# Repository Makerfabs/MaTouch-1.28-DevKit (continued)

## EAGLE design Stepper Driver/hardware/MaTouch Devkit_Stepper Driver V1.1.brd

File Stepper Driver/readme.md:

# MaTouch1.28" Devkit Stepper Driver

```c++
/*
Library version:
Arduino IDE 2.3.4
esp32 V3.1.1
GFX Library for Arduino v1.5.4
lvgl v8.3.11
RTClib v2.1.4
Adafruit BusIO v1.16.2
ESP32Time v2.0.6

Tools:
USB CDC On Boot: Enabled
Flash size: 16MB(128Mb)
Partition Schrme: 16M Flash(3MB APP/9.9MB FATFS)
PSRAM: OPI PSRAM
*/
```
## Introduce

1.[How to use?](https://wiki.makerfabs.com/Matouch%201.28%20DevKit.html#25-step-motor-driver)

2.[How to upload code?](https://wiki.makerfabs.com/Matouch%201.28%20DevKit.html#35-step-motor-driver)

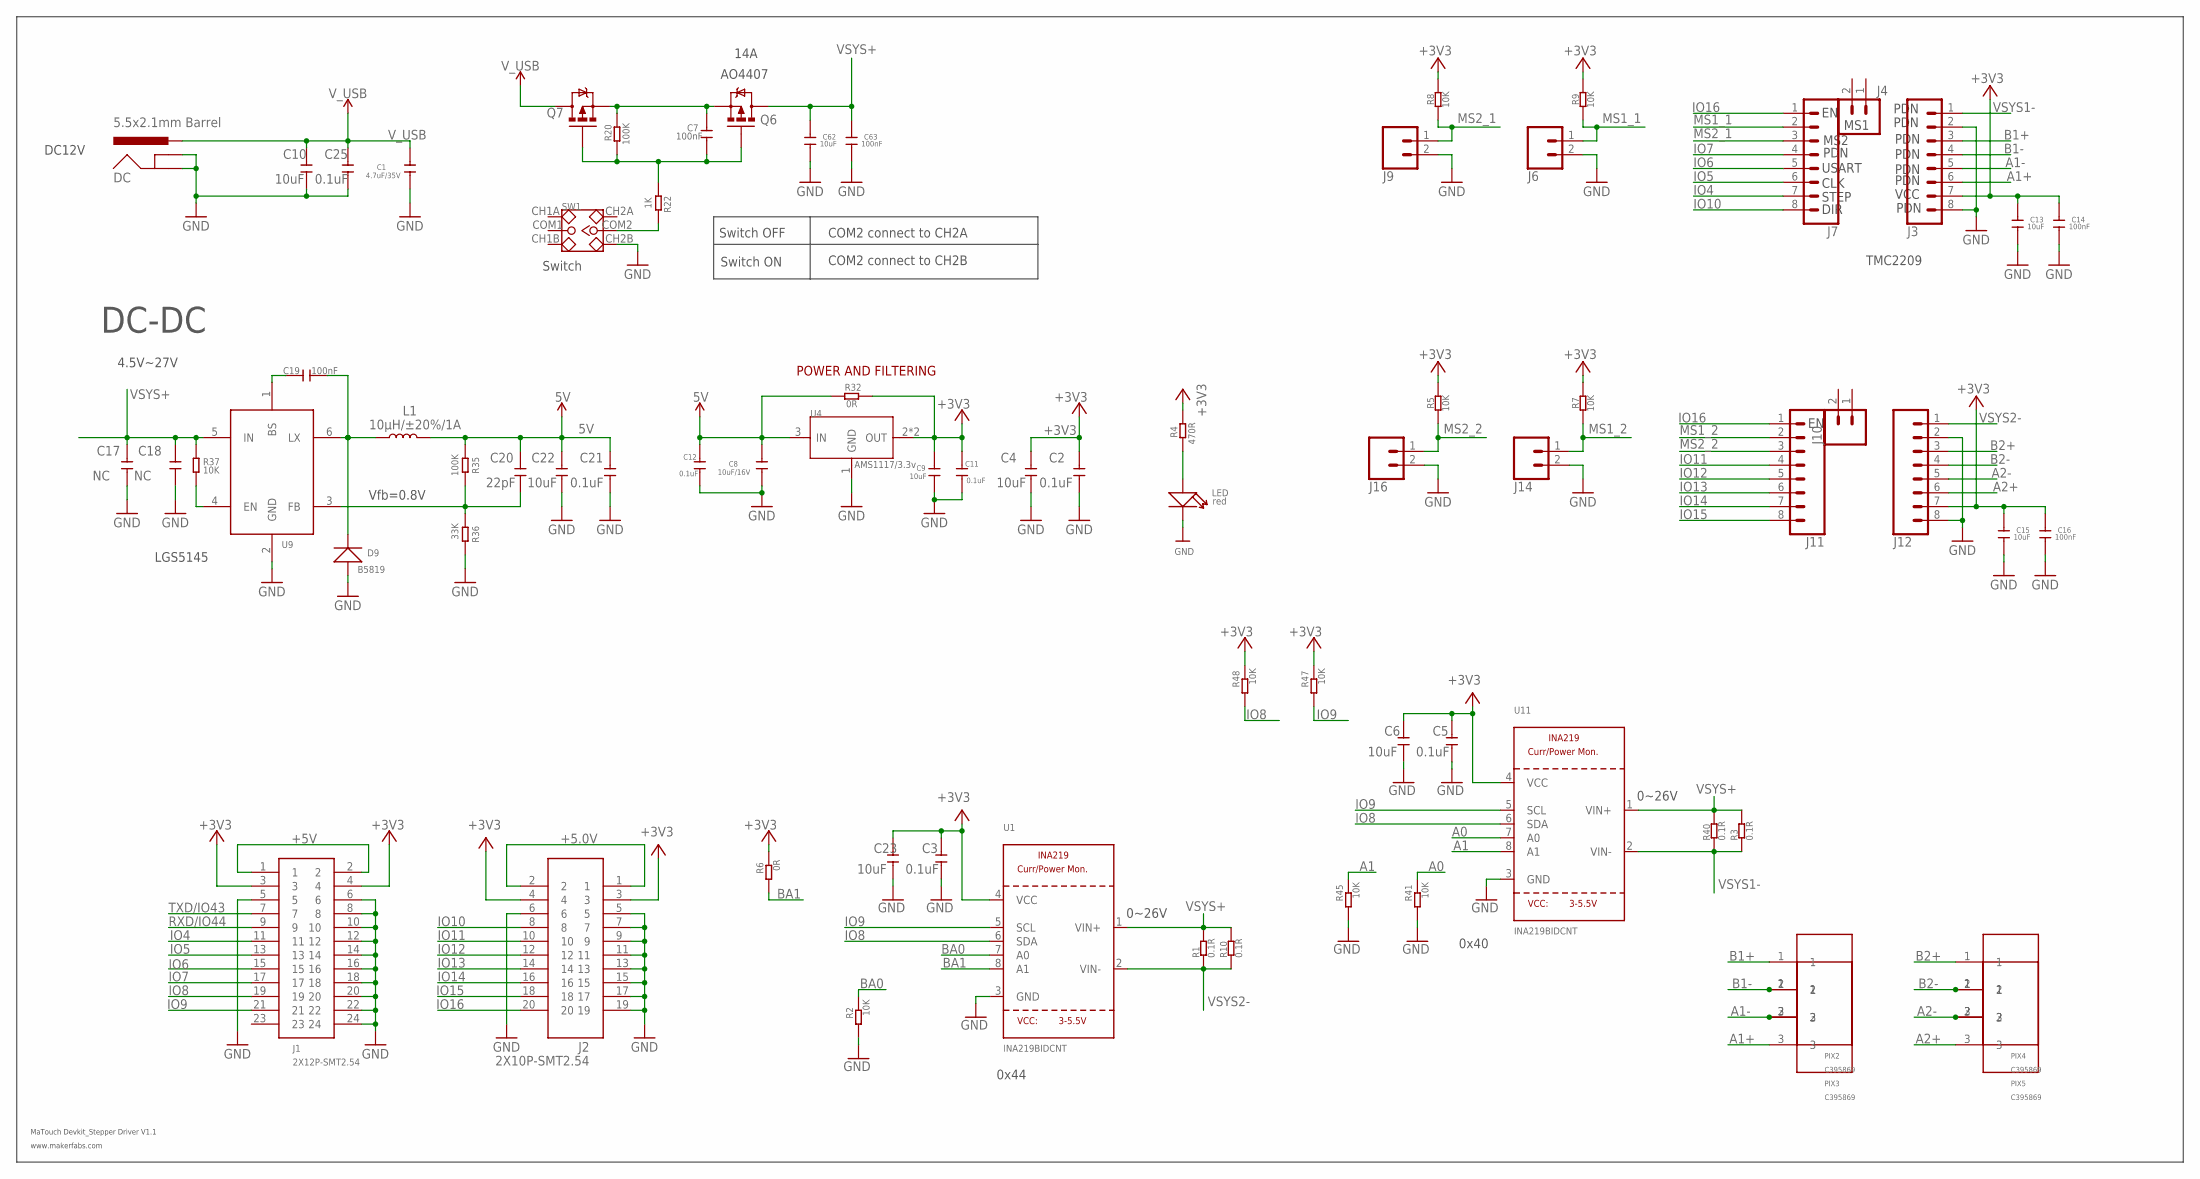
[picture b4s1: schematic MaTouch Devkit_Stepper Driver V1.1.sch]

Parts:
C1: 4.7uF/35V; 0603
C2, C3, C5, C11, C12, C21, C25: 0.1uF; 0603
C4, C6, C9, C10, C13, C15, C22, C23, C62: 10uF; 0603
C7, C14, C16, C19, C63: 100nF; 0603
C8: 10uF/16V; 0603
C17, C18: NC; 0603
C20: 22pF; 0603
D9: B5819; SOD123
DC: 5.5x2.1mm Barrel; POWER_JACK_SMD
J1: 2X12P-SMT2.54
J2: 2X10P-SMT2.54
J3, J7, J11, J12: CONN_08"; 1X08
J4, J6, J9, J10, J14, J16: CONN_02LOCK; 1X02_LOCK
L1: 10µH/±20%/1A; SRN6045
LED: red; DISCRETE_LED-0603
PIX2, PIX3, PIX4, PIX5: C395869; PIN_3P
Q6, Q7: MOSFET-PCHANNELFDS6675; SO08
R1, R3, R10, R40: 0.1R; DISCRETE_R2512
R2, R5, R7, R8, R9, R37, R41, R45, R47, R48: 10K; R0603
R4: 470R; R0603
R6, R32: 0R; R0603
R20, R35: 100K; R0603
R22: 1K; R0603
R36: 33K; R0603
SW1: SWITCH-2CH-6P'90D'; 6P-2CH-2.54-9.0X3.6-90D
U1, U11: INA219BIDCNT; SOT23-8
U4: AMS1117/3.3v; SOT89
U9: SY8201ABC; SOT-23-6

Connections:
5V: C8.1, C12.2, C20.2, C21.2, C22.2, L1.2, R32.1, R35.1, U4.3 (IN)
+3V3: C2.2, C3.2, C4.2, C5.2, C6.2, C9.1, C11.2, C13.2, C14.2, C15.2, C16.2, C23.2, J1.3, J1.4, J2.3, J2.4, J3.7, J12.7, R4.2, R5.2, R6.2, R7.2, R8.2, R9.2, R32.2, R47.2, R48.2, U1.4 (VCC), U4.2 (OUT), U4.4 (OUT), U11.4 (VCC)
+5.0V: J2.1, J2.2
+5V: J1.1, J1.2
A0: R41.2, U11.7 (A0)
A1: R45.2, U11.8 (A1)
A1+: J3.6, PIX3.3
A1-: J3.5, PIX2.3, PIX3.2
A2+: J12.6, PIX5.3
A2-: J12.5, PIX4.3, PIX5.2
B1+: J3.3, PIX2.1
B1-: J3.4, PIX2.2, PIX3.1
B2+: J12.3, PIX4.1
B2-: J12.4, PIX4.2, PIX5.1
BA0: R2.2, U1.7 (A0)
BA1: R6.1, U1.8 (A1)
GND: C1.2, C2.1, C3.1, C4.1, C5.1, C6.1, C8.2, C9.2, C10.1, C11.1, C12.1, C13.1, C14.1, C15.1, C16.1, C17.1, C18.1, C21.1, C22.1, C23.1, C25.1, C62.1, C63.1, D9.+, DC.GND (GNDBREAK), DC.P$4 (GND), J1.5, J1.6, J1.8, J1.10, J1.12, J1.14, J1.16, J1.18, J1.20, J1.22, J1.24, J2.5, J2.6, J2.7, J2.9, J2.11, J2.13, J2.15, J2.17, J2.19, J3.2, J3.8, J6.2, J9.2, J12.2, J12.8, J14.2, J16.2, LED.-, R2.1, R36.2, R41.1, R45.1, SW1.CH2B, U1.3 (GND), U4.1 (GND), U9.2 (GND), U11.3 (GND)
IO4: J1.11, J7.7
IO5: J1.13, J7.6
IO6: J1.15, J7.5
IO7: J1.17, J7.4
IO8: J1.19, R48.1, U1.6 (SDA), U11.6 (SDA)
IO9: J1.21, R47.1, U1.5 (SCL), U11.5 (SCL)
IO10: J2.8, J7.8
IO11: J2.10, J11.4
IO12: J2.12, J11.5
IO13: J2.14, J11.6
IO14: J2.16, J11.7
IO15: J2.18, J11.8
IO16: J2.20, J7.1, J11.1
MS1_1: J6.1, J7.2, R9.1
MS1_2: J11.2, J14.1, R7.1
MS2_1: J7.3, J9.1, R8.1
MS2_2: J11.3, J16.1, R5.1
unnamed: LED.+, R4.1
unnamed: C7.1, Q6.4 (G), Q7.4 (G), R20.2, R22.2
unnamed: R22.1, SW1.COM2
unnamed: C19.2, D9.-, L1.1, U9.6 (LX)
unnamed: C19.1, U9.1 (BS)
unnamed: C20.1, R35.2, R36.1, U9.3 (FB)
unnamed: R37.2, U9.4 (EN)
unnamed: C7.2, Q6.1 (S), Q6.2 (S), Q6.3 (S), Q7.1 (S), Q7.2 (S), Q7.3 (S), R20.1
RXD/IO44: J1.9
TXD/IO43: J1.7
VSYS1-: J3.1, R3.1, R40.1, U11.2 (VIN-)
VSYS2-: J12.1, R1.1, R10.1, U1.2 (VIN-)
VSYS+: C17.2, C18.2, C62.2, C63.2, Q6.5 (D), Q6.6 (D), Q6.7 (D), Q6.8 (D), R1.2, R3.2, R10.2, R37.1, R40.2, U1.1 (VIN+), U9.5 (IN), U11.1 (VIN+)
V_USB: C1.1, C10.2, C25.2, DC.VIN0 (PWR), Q7.5 (D), Q7.6 (D), Q7.7 (D), Q7.8 (D)

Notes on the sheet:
MaTouch Devkit_Stepper Driver V1.1
www.makerfabs.com
DC-DC
Switch OFF
Switch ON
COM2 connect to CH2A
COM2 connect to CH2B
Vfb=0.8V
4.5V~27V
0~26V
DC12V
AO4407
14A
Switch
POWER AND FILTERING
PDN
USART
CLK
STEP
DIR
VCC
MS1
MS2
LGS5145
TMC2209
0x40
0x44

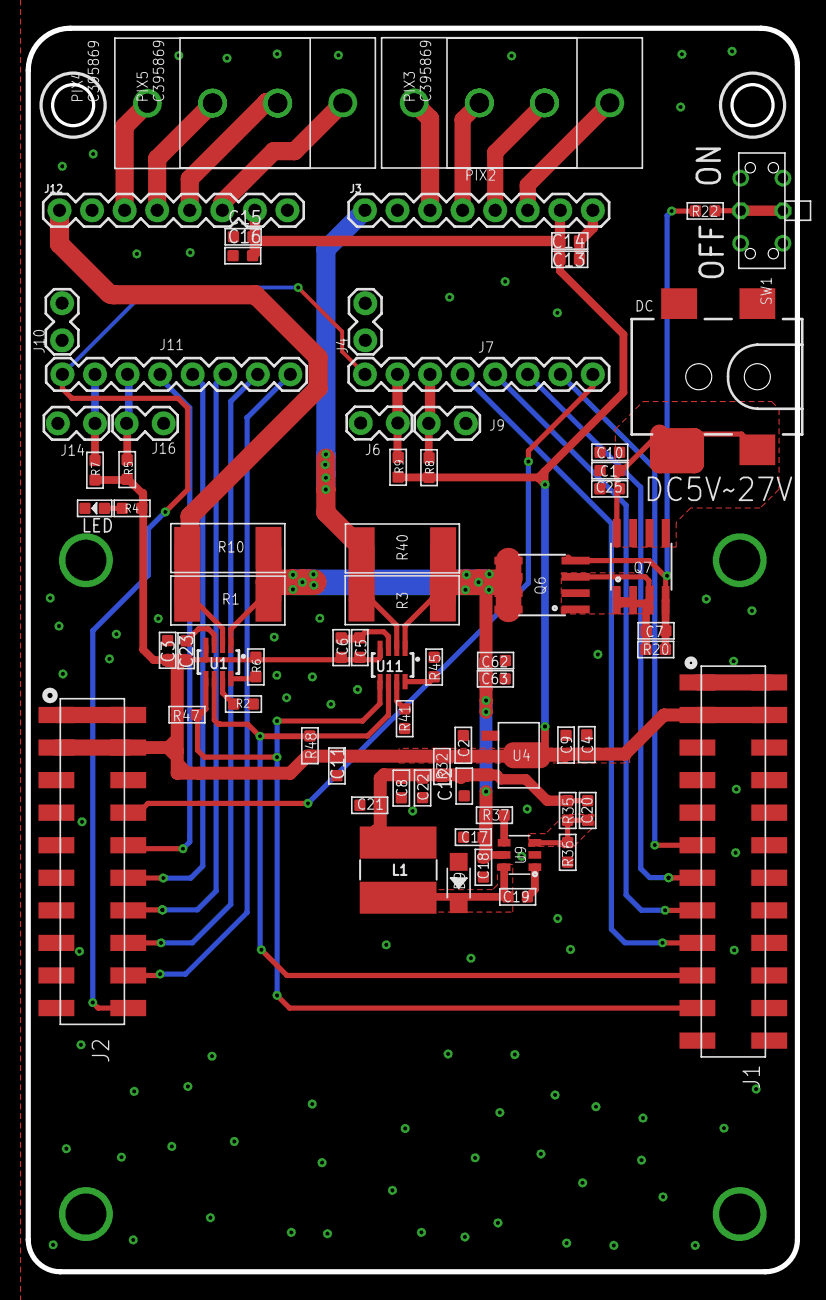
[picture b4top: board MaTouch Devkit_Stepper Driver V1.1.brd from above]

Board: 2 copper layers, 60.0 x 97.0 mm, 75 parts (1 on the bottom side), 46 nets.

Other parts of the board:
U$2: MAKERFABS_0.3

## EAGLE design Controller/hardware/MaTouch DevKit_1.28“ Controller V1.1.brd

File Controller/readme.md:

# MaTouch1.28" DevKit Controller

## Intruduce

The MaTouch 1.28" ToolSet_Controller is an ESP32-S3-based round touch controller, with haptic feedback, RTC, and more expansion interfaces for a smarter and richer interactive experience.

[YouTube Video](https://youtu.be/dvfv04e7QA0)

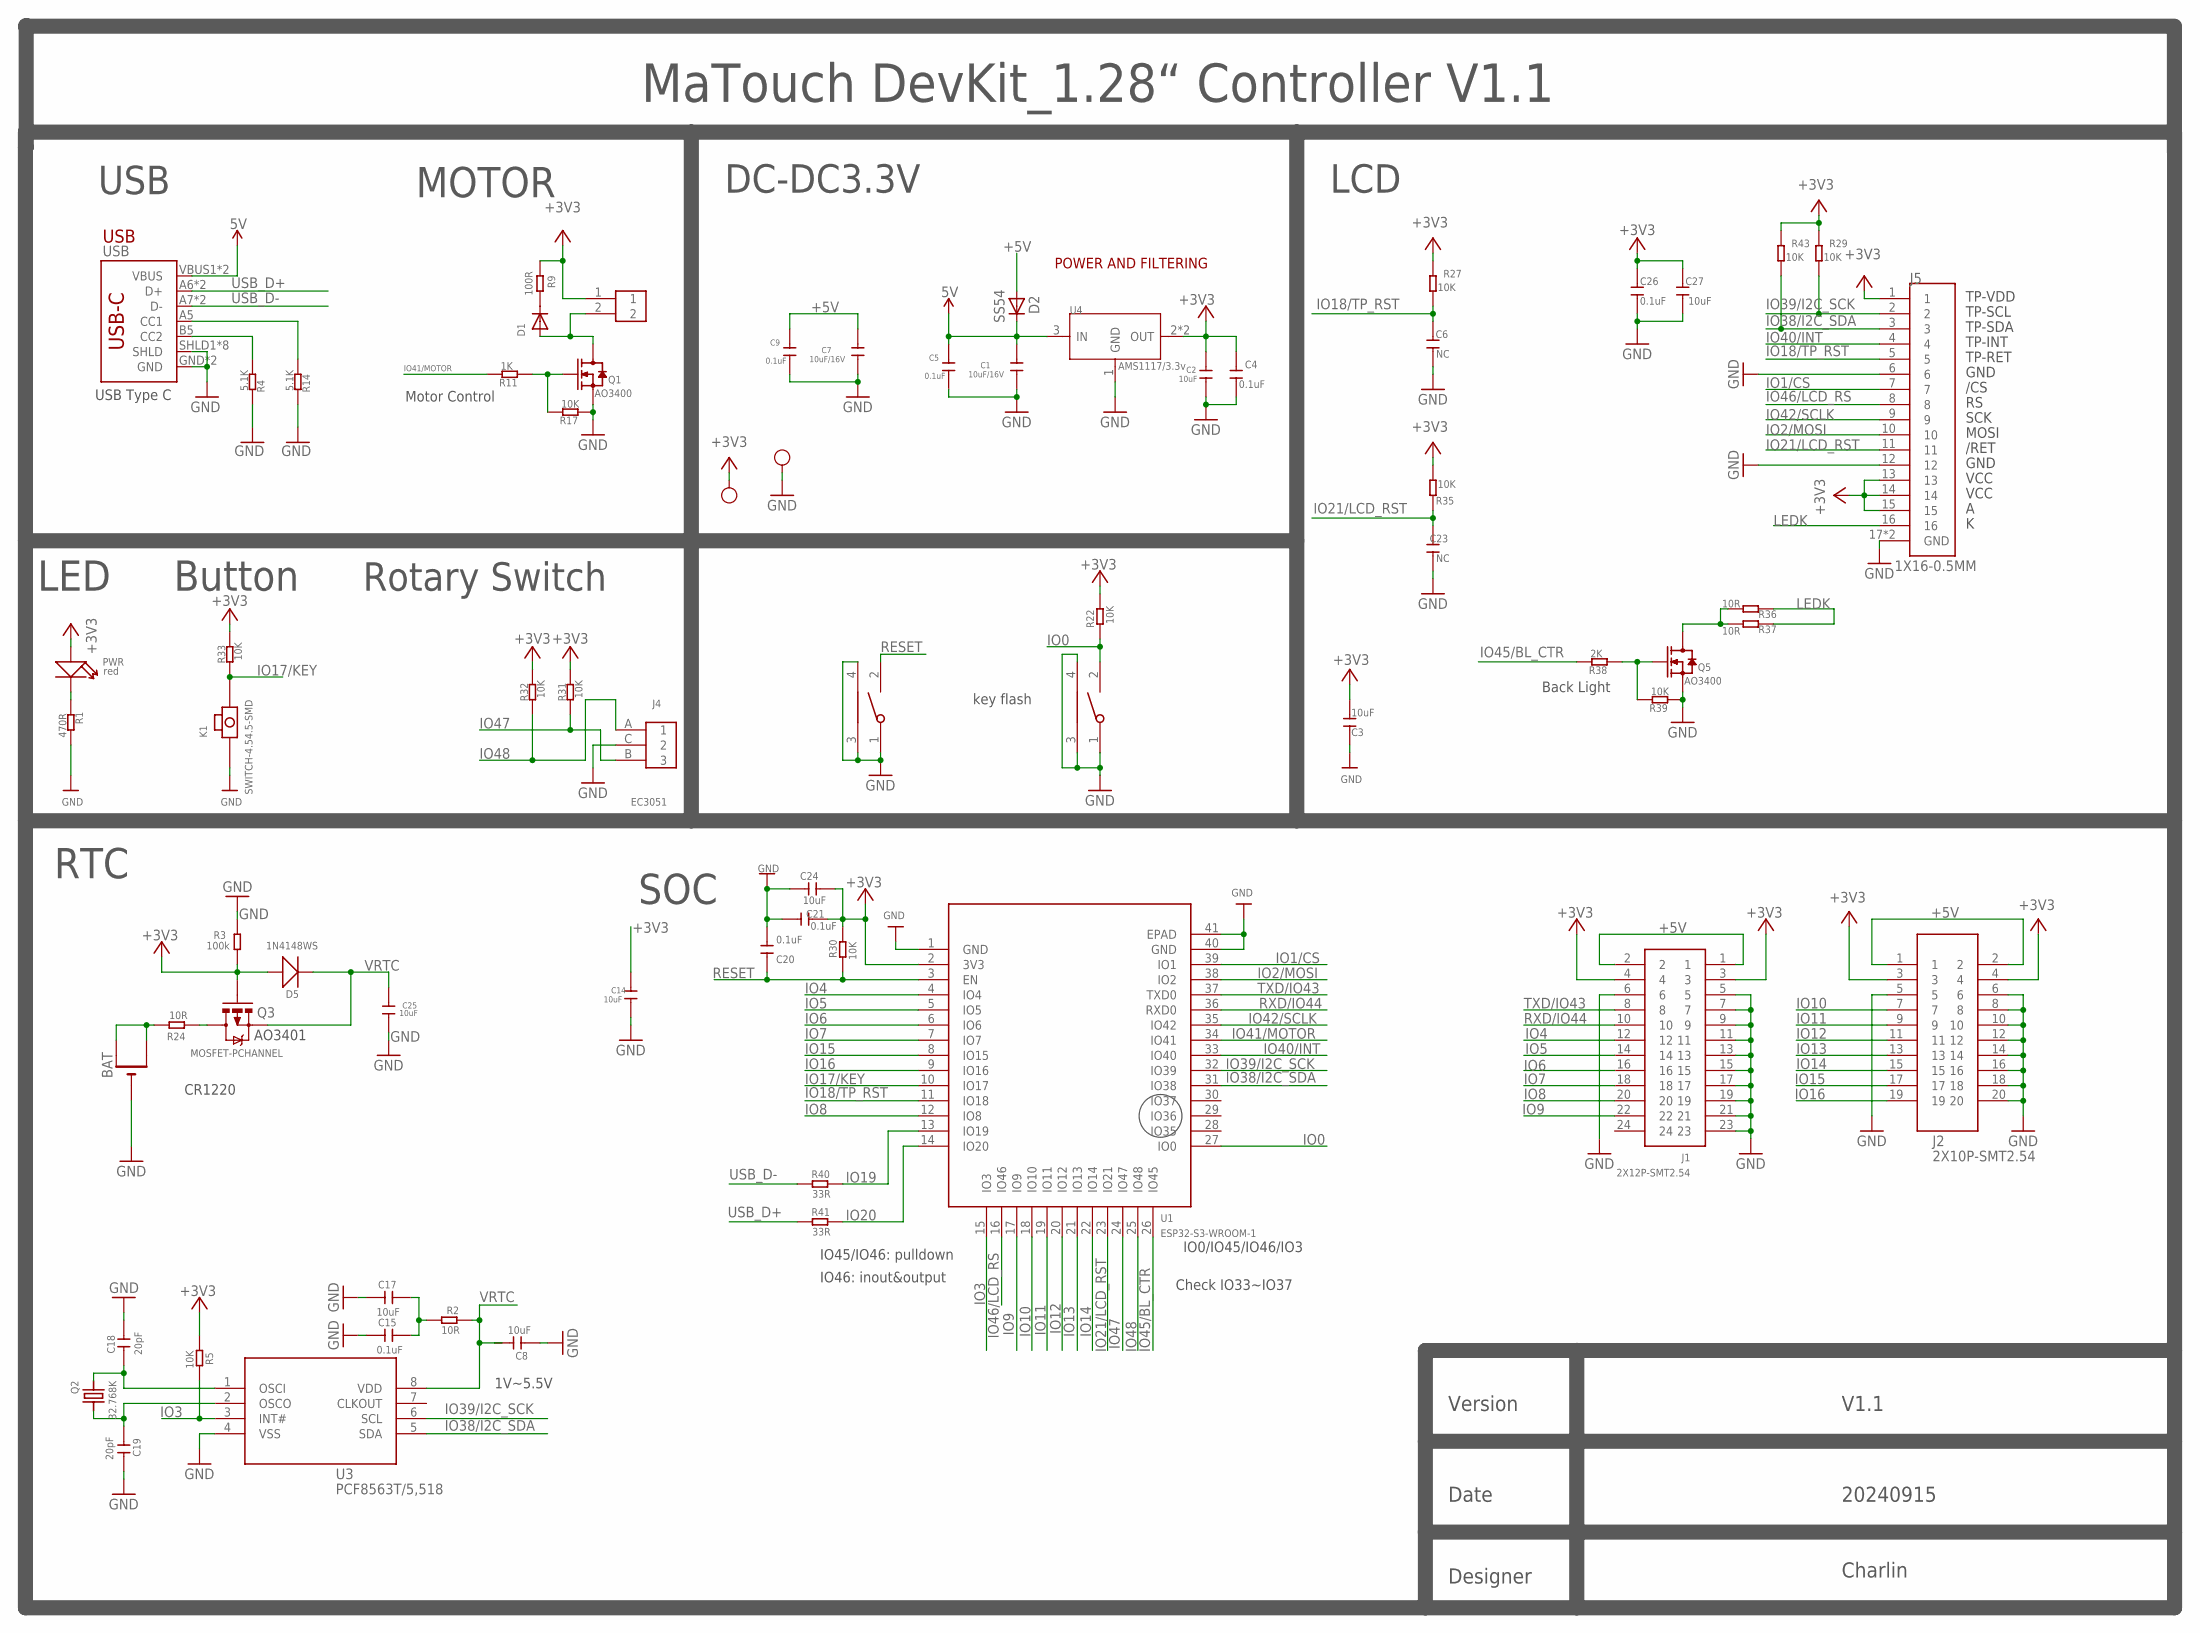
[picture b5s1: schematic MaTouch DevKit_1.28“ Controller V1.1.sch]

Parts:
3V3: TEST-POINT'4545'; TP-D45MIL; PARTNO DNP
BAT: CR1220SMT; CR1220-SMD
BOOT: TS24CA; 2*4*3.5MM
C1, C7: 10uF/16V; 0603
C2, C14, C25: 10uF; 0603
C3, C8, C17, C24: 10uF; DISCRETE_C0603
C4, C26: 0.1uF; DISCRETE_C0402
C5, C9: 0.1uF; 0603
C6, C23: NC; DISCRETE_C0402
C15, C20, C21: 0.1uF; DISCRETE_C0603
C18, C19: 20pF; DISCRETE_C0603
C27: 10uF; DISCRETE_C0402
D1: DIODESOD-323F; SOD-323F
D2: SS54; DO-214AC
D5: 1N4148WS; SOD323
GND: TEST-POINT'4545'; TP-D45MIL; PARTNO DNP
J1: 2X12P-SMT2.54
J2: 2X10P-SMT2.54
J4: EC3051; MAKERFABS_EC3051
J5: 1X16-0.5MM
K1: SWITCH-4.54.5-SMD; SWITCH-4.5*4.5-SMD
MOTOR: CN-1.02P; SH1.0-2P-SMD
PWR: red; DISCRETE_LED-0603
Q1, Q5: AO3400; SOT23@1
Q2: 32.768K; XTAL3215
Q3: MOSFET-PCHANNEL; SOT23-3
R1: 470R; DISCRETE_R0402
R2, R24: 10R; R0603
R3: 100k; R0603
R4, R14: 5.1K; DISCRETE_R0402
R5, R22, R30: 10K; R0603
R9: 100R; DISCRETE_R0402
R11: 1K; DISCRETE_R0402
R17, R27, R29, R31, R32, R33, R35, R39, R43: 10K; DISCRETE_R0402
R36, R37: 10R; DISCRETE_R0402
R38: 2K; DISCRETE_R0402
R40, R41: 33R; R0603
RST: TS24CA; 2*4*3.5MM
U1: ESP32-S3-WROOM-1
U3: PCF8563T/5,518; SOP8
U4: AMS1117/3.3v; SOT89
USB: USB_C5; USB-C-16P-5

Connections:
5V: C1.1, C5.1, D2.C, U4.3 (IN), USB.VBUS1 (VBUS), USB.VBUS2 (VBUS)
+3V3: 3V3.T, C2.1, C3.2, C4.2, C14.1, C21.1, C24.1, C26.2, C27.2, D5.+, J1.3, J1.4, J2.3, J2.4, J5.1, J5.13, J5.14, J5.15, MOTOR.1, PWR.+, Q3.1 (G), R3.1, R5.1, R9.1, R22.2, R27.2, R29.2, R30.2, R31.1, R32.1, R33.1, R35.2, R43.2, U1.2 (3V3), U4.2 (OUT), U4.4 (OUT)
+5V: C7.1, C9.1, D2.A, J1.1, J1.2, J2.1, J2.2
GND: BAT.-, BOOT.1, BOOT.3, BOOT.4, C1.2, C2.2, C3.1, C4.1, C5.2, C6.1, C7.2, C8.1, C9.2, C14.2, C15.1, C17.1, C18.2, C19.2, C20.2, C21.2, C23.1, C24.2, C25.1, C26.1, C27.1, GND.T, J1.5, J1.6, J1.7, J1.9, J1.11, J1.13, J1.15, J1.17, J1.19, J1.21, J1.23, J2.5, J2.6, J2.8, J2.10, J2.12, J2.14, J2.16, J2.18, J2.20, J4.C (2), J5.6, J5.12, J5.17 (GND), J5.18 (GND), K1.1, K1.4 (1), Q1.2 (S), Q5.2 (S), R1.1, R3.2, R4.2, R14.2, R17.1, R39.1, RST.1, RST.3, RST.4, U1.1 (GND), U1.40 (GND), U1.41 (EPAD), U3.4 (VSS), U4.1 (GND), USB.GND, USB.GND2 (GND), USB.SHLD1 (SHLD), USB.SHLD2 (SHLD), USB.SHLD3 (SHLD), USB.SHLD4 (SHLD), USB.SHLD5 (SHLD), USB.SHLD6 (SHLD), USB.SHLD7 (SHLD), USB.SHLD8 (SHLD)
IO0: BOOT.2, R22.1, U1.27 (IO0)
IO1/CS: J5.7, U1.39 (IO1)
IO2/MOSI: J5.10, U1.38 (IO2)
IO3: R5.2, U1.15 (IO3), U3.3 (INT#)
IO4: J1.12, U1.4 (IO4)
IO5: J1.14, U1.5 (IO5)
IO6: J1.16, U1.6 (IO6)
IO7: J1.18, U1.7 (IO7)
IO8: J1.20, U1.12 (IO8)
IO9: J1.22, U1.17 (IO9)
IO10: J2.7, U1.18 (IO10)
IO11: J2.9, U1.19 (IO11)
IO12: J2.11, U1.20 (IO12)
IO13: J2.13, U1.21 (IO13)
IO14: J2.15, U1.22 (IO14)
IO15: J2.17, U1.8 (IO15)
IO16: J2.19, U1.9 (IO16)
IO17/KEY: K1.2, K1.3 (2), R33.2, U1.10 (IO17)
IO18/TP_RST: C6.2, J5.5, R27.1, U1.11 (IO18)
IO19: R40.2, U1.13 (IO19)
IO20: R41.2, U1.14 (IO20)
IO21/LCD_RST: C23.2, J5.11, R35.1, U1.23 (IO21)
IO38/I2C_SDA: J5.3, R43.1, U1.31 (IO38), U3.5 (SDA)
IO39/I2C_SCK: J5.2, R29.1, U1.32 (IO39), U3.6 (SCL)
IO40/INT: J5.4, U1.33 (IO40)
IO41/MOTOR: R11.2, U1.34 (IO41)
IO42/SCLK: J5.9, U1.35 (IO42)
IO45/BL_CTR: R38.2, U1.26 (IO45)
IO46/LCD_RS: J5.8, U1.16 (IO46)
IO47: J4.B (3), R31.2, U1.24 (IO47)
IO48: J4.A (1), R32.2, U1.25 (IO48)
LEDK: J5.16, R36.1, R37.1
M-: D1.A, MOTOR.2, Q1.3 (D)
unnamed: Q1.1 (G), R11.1, R17.2
unnamed: C15.2, C17.2, R2.1
unnamed: BAT.+$1 (+), BAT.+$2 (+1), R24.2
unnamed: C18.1, Q2.P$1 (1), U3.1 (OSCI)
unnamed: R14.1, USB.A5 (CC1)
unnamed: PWR.-, R1.2
unnamed: D1.C, R9.2
unnamed: C19.1, Q2.P$2 (2), U3.2 (OSCO)
unnamed: R4.1, USB.B5 (CC2)
unnamed: Q3.3 (D), R24.1
unnamed: Q5.1 (G), R38.1, R39.2
unnamed: Q5.3 (D), R36.2, R37.2
RESET: C20.1, R30.1, RST.2, U1.3 (EN)
RXD/IO44: J1.10, U1.36 (RXD0)
TXD/IO43: J1.8, U1.37 (TXD0)
USB_D+: R41.1, USB.A6 (D+), USB.B6 (D+)
USB_D-: R40.1, USB.A7 (D-), USB.B7 (D-)
VRTC: C8.2, C25.2, D5.-, Q3.2 (S), R2.2, U3.8 (VDD)

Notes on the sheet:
key flash
RTC
Button
Rotary Switch
DC-DC3.3V
USB
LCD
MaTouch DevKit_1.28“ Controller V1.1
Back Light
LED
Version
Date
Designer
V1.1
20240915
Charlin
VCC
GND
/RET
MOSI
SCK
/CS
TP-RET
TP-INT
TP-SDA
TP-SCL
TP-VDD
USB Type C
Motor Control
MOTOR
IO45/IO46: pulldown
IO46: inout&output
IO0/IO45/IO46/IO3
Check IO33~IO37
SOC
POWER AND FILTERING
1V~5.5V
AO3401
CR1220

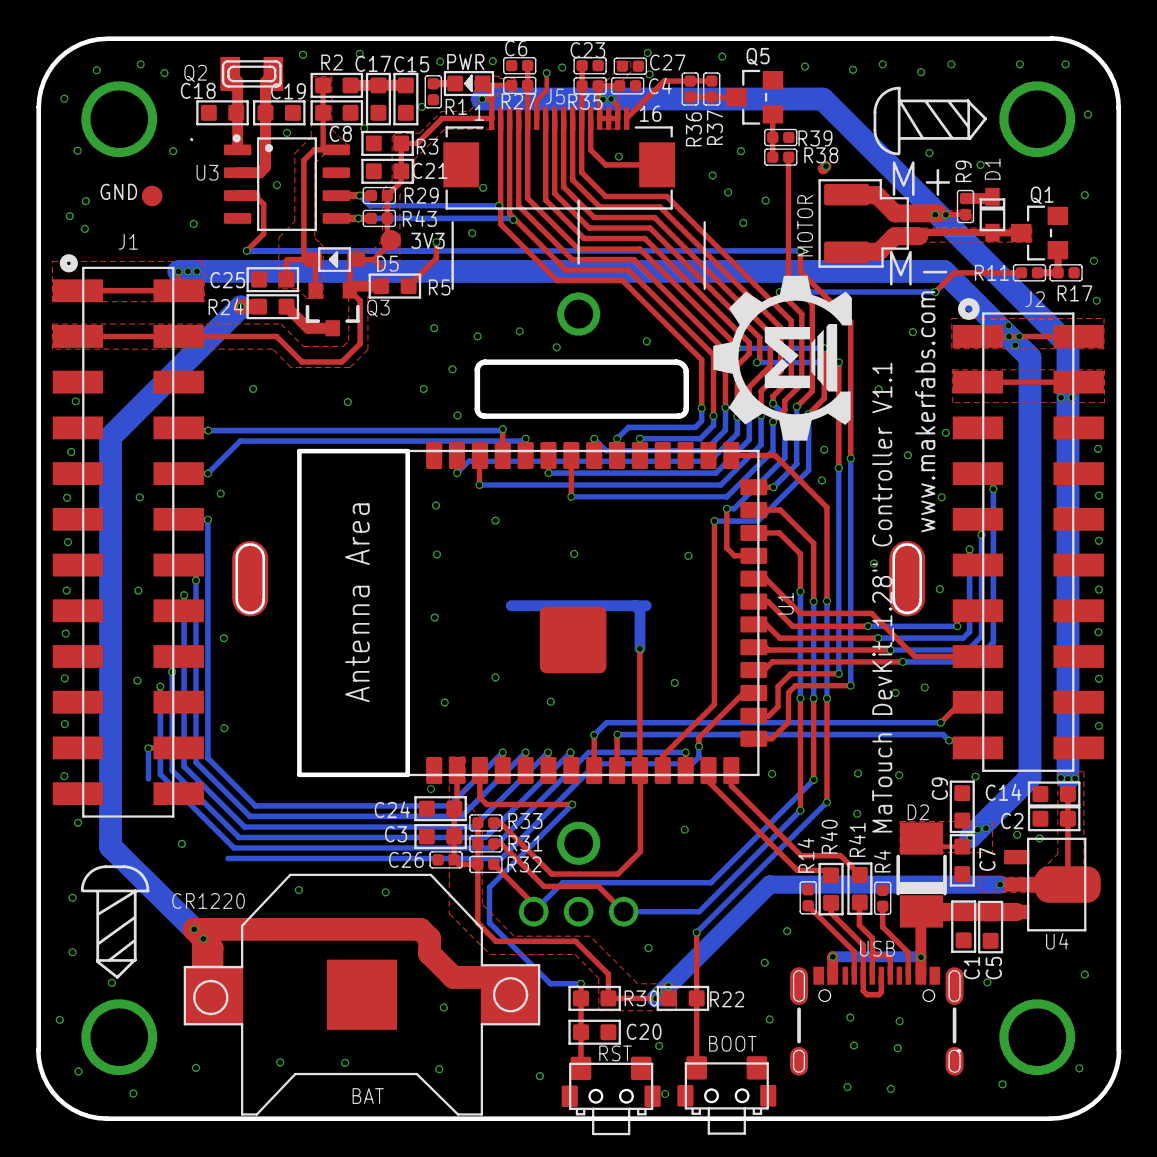
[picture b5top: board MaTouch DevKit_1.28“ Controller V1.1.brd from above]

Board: 2 copper layers, 60.0 x 60.0 mm, 70 parts (1 on the bottom side), 55 nets.

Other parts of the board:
U$1: MAKERFABS_0.3

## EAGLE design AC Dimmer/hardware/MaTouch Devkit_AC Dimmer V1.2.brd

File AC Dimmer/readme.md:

# MaTouch1.28" Devkit AC Dimmer

```c++
/*
Library version:
Arduino IDE 2.3.4
esp32 V3.1.1
GFX Library for Arduino v1.5.3
lvgl v8.3.11

Tools:
USB CDC On Boot: Enabled
Flash size:16MB(128Mb)
Partition Schrme:16M Flash(3MB APP/9.9MB FATFS)
PSRAM: OPI PSRAM

Note:
2025/2/12   添加开关按钮设置
*/
```
## Introduce

1.[How to use?](https://wiki.makerfabs.com/Matouch%201.28%20DevKit.html#27-ac-dimmer)

2.[How to upload code?](https://wiki.makerfabs.com/Matouch%201.28%20DevKit.html#37-ac-dimmer)

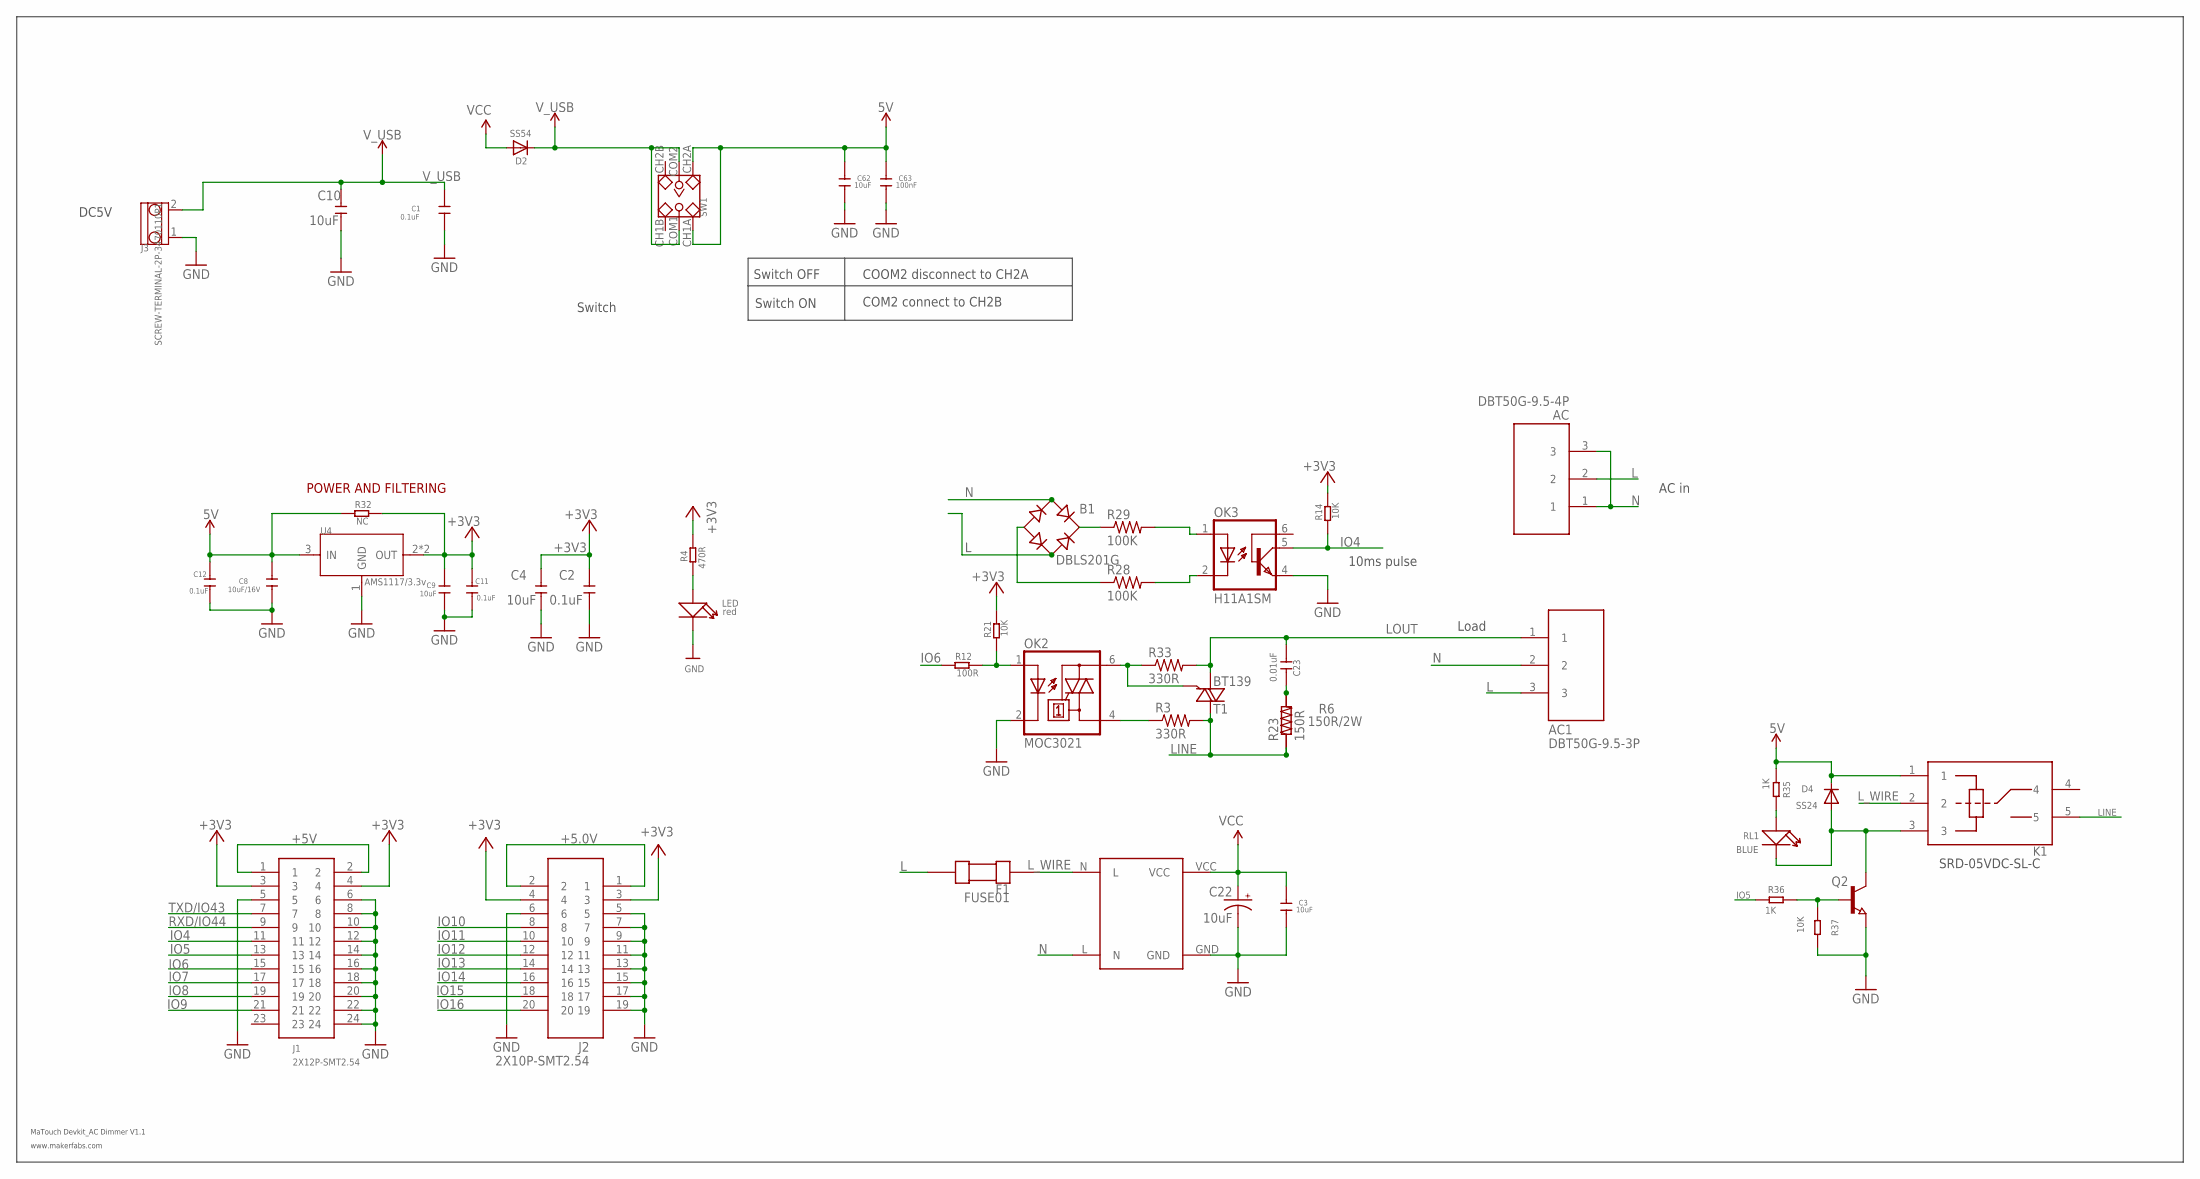
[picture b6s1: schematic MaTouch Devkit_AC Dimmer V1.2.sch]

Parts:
AC: DBT50G-9.5-4P; THROUGH-HOLE-9.5
AC1: DBT50G-9.5-3P; THROUGH-HOLE-9.5
B1: DBLS201G; DBS
C1, C2, C11, C12: 0.1uF; 0603
C3, C4, C9, C10, C62: 10uF; 0603
C8: 10uF/16V; 0603
C22: 10uF; EIA3528-KIT
C23: 0.01uF; DISCRETE_C0512/10.18
C63: 100nF; 0603
D2: SS54; SMADIODE
D4: SS24; SMADIODE
F1: FUSE01
J1: 2X12P-SMT2.54
J2: 2X10P-SMT2.54
J3: SCREW-TERMINAL-2P-3470110P1; 2P-5.0
K1: JQC3FF; DIP5_JQC3FF
LED: red; DISCRETE_LED-0603
OK2: MOC3021; DIL6-SMD
OK3: H11A1SM; DIL6-SMD
Q2: NPN-TRANSISTOR_SOT23; SOT23
R3, R33: 330R; 1206
R4: 470R; R0603
R6: 150R/2W; R-0617
R12: 100R; R0603
R14, R21, R37: 10K; R0603
R23: 150R; V234/12
R28, R29: 100K; 1206
R32: NC; R0603
R35, R36: 1K; R0603
RL1: BLUE; LED-0603
SW1: SWITCH-2CH-6P'90D'; 6P-2CH-2.54-9.0X3.6-90D
T1: BT139; TO220AB
U4: AMS1117/3.3v; SOT89
U5: AC-DCHLK01; HLK-PM01

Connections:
5V: C8.1, C12.2, C62.2, C63.2, D4.C, K1.1, R32.1, R35.1, SW1.CH1A, SW1.CH2A, U4.3 (IN)
+3V3: C2.2, C4.2, C9.1, C11.2, J1.3, J1.4, J2.3, J2.4, R4.2, R14.2, R21.2, R32.2, U4.2 (OUT), U4.4 (OUT)
+5.0V: J2.1, J2.2
+5V: J1.1, J1.2
GND: C1.2, C2.1, C3.1, C4.1, C8.2, C9.2, C10.1, C11.1, C12.1, C22.C (-), C62.1, C63.1, J1.5, J1.6, J1.8, J1.10, J1.12, J1.14, J1.16, J1.18, J1.20, J1.22, J1.24, J2.5, J2.6, J2.7, J2.9, J2.11, J2.13, J2.15, J2.17, J2.19, J3.1, LED.-, OK2.2 (C), OK3.4 (EMI), Q2.2 (E), R37.2, U4.1 (GND), U5.GND
IO4: J1.11, OK3.5 (COL), R14.1
IO5: J1.13, R36.1
IO6: J1.15, R12.1
IO7: J1.17
IO8: J1.19
IO9: J1.21
IO10: J2.8
IO11: J2.10
IO12: J2.12
IO13: J2.14
IO14: J2.16
IO15: J2.18
IO16: J2.20
L: AC.2, AC1.3, B1.AC2, F1.P$2
LINE: K1.5, R3.2, R6.1, R23.1, T1.2 (A2)
LOUT: AC1.1, C23.P$2 (2), R33.2, T1.1 (A1)
L_WIRE: F1.P$1, K1.2, U5.N (L)
N: AC.1, AC.3, AC1.2, B1.AC1, U5.L (N)
unnamed: C23.P$1 (1), R6.2, R23.2
unnamed: LED.+, R4.1
unnamed: OK2.1 (A), R12.2, R21.1
unnamed: B1.-, R28.1
unnamed: OK2.4 (A1), R3.1
unnamed: B1.+, R29.1
unnamed: OK3.1 (A), R29.2
unnamed: OK3.2 (C), R28.2
unnamed: OK2.6 (A2), R33.1, T1.3 (G)
unnamed: R35.2, RL1.+
unnamed: D4.A, K1.3, Q2.3 (C), RL1.-
unnamed: Q2.1 (B), R36.2, R37.1
RXD/IO44: J1.9
TXD/IO43: J1.7
VCC: C3.2, C22.A (+), D2.A, U5.VCC
V_USB: C1.1, C10.2, D2.C, J3.2, SW1.COM1, SW1.COM2

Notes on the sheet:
MaTouch Devkit_AC Dimmer V1.1
www.makerfabs.com
Switch OFF
Switch ON
COOM2 disconnect to CH2A
COM2 connect to CH2B
DC5V
Switch
POWER AND FILTERING
Load
AC in
10ms pulse
SRD-05VDC-SL-C

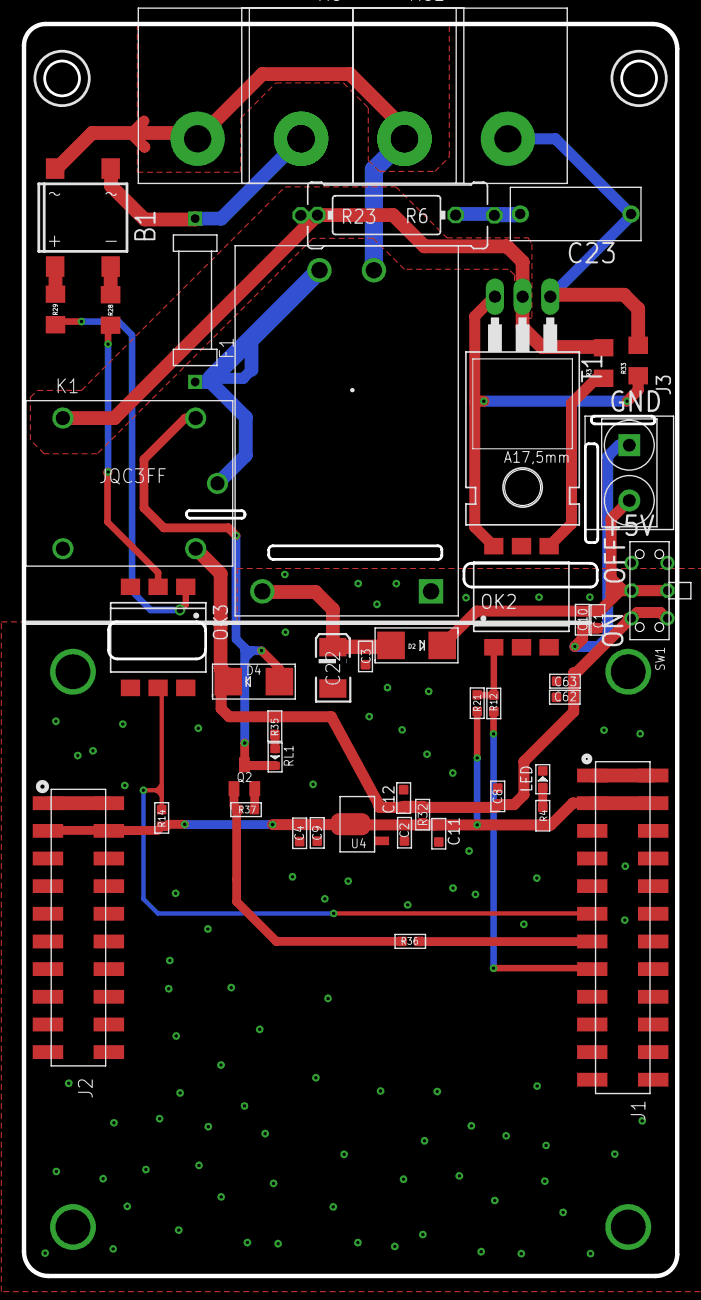
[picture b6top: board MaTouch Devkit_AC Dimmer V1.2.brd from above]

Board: 2 copper layers, 60.0 x 115.0 mm, 47 parts (1 on the bottom side), 27 nets.

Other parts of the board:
U$2: MAKERFABS_0.3
